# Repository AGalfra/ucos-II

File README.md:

# ucos-II

## Sensor de Temperatura ST-1820

Introducción

Este dispositivo desarrollado en el presente informe es un medidor de temperaturas basado en sensores 1-Wire del tipo  capaz de medir hasta 4 sensores simultáneamente (aunque esta limitación está dada solo por configuración del firmware para adaptarla a las opciones del menú).
Tiene además la posibilidad de modificar la escala de medición, es decir, en ºC y ºF.
También es configurable la frecuencia de adquisición de los sensores (3, 5 o 10 segundos).
Para la visualización de las temperaturas se pueden elegir entre 2 modos de operación que serán descritos más adelante.

Diseño del PCB en Kicad
Desarrollo del firmware en STM32CubeIDE con kernel U/COS-II
Descripción
 
Para este proyecto se utilizó la placa de desarrollo Blue Pill que cuenta con un microprocesador ARM Cortex-M3 STM32F103C8T6 de ST Microelectronics en el cual se ha embebido el Kernel v2.9216. 

Además de la placa de desarrollo se han utilizado los siguientes elementos:

-Pantalla OLED SSD1306 128x64 pixeles de 0.96” con comunicación I2C.

-Encoder rotativo, que es utilizado para controlar el dispositivo.

-Sensores de temperatura del tipo 1-Wire como por ej. los DS18B20, DS1820 o DS18S20.

-UART para poder realizar una conexión con la PC (para un menú de diagnóstico).

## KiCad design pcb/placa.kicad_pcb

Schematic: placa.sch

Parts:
J1, J2, J3, J4: Conn_01x03; PinHeader_1x03_P2.54mm_Horizontal
J5: UART; PinHeader_1x04_P2.54mm_Vertical
J6: Encoder; Encoder_Rotativo
R1: 4K7; R_Axial_DIN0204_L3.6mm_D1.6mm_P7.62mm_Horizontal
U1: Blue_Pill
U2: SSD1306

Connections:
+3V3: J1.3, J2.3, J3.3, J4.3, J5.1, J6.2, R1.1, U1.18, U1.40, U2.2
/DQ: J1.2, J2.2, J3.2, J4.2, R1.2, U1.30
/EBUT: J6.3, U1.31
/ENCA: J6.4, U1.13
/ENCB: J6.5, U1.14
/RX: J5.2, U1.27
/SCL: U1.34, U2.3
/SDA: U1.35, U2.4
/TX: J5.3, U1.26
GND: J1.1, J2.1, J3.1, J4.1, J5.4, J6.1, U1.19, U1.20, U1.39, U2.1

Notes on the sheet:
BUS ONEWIRE

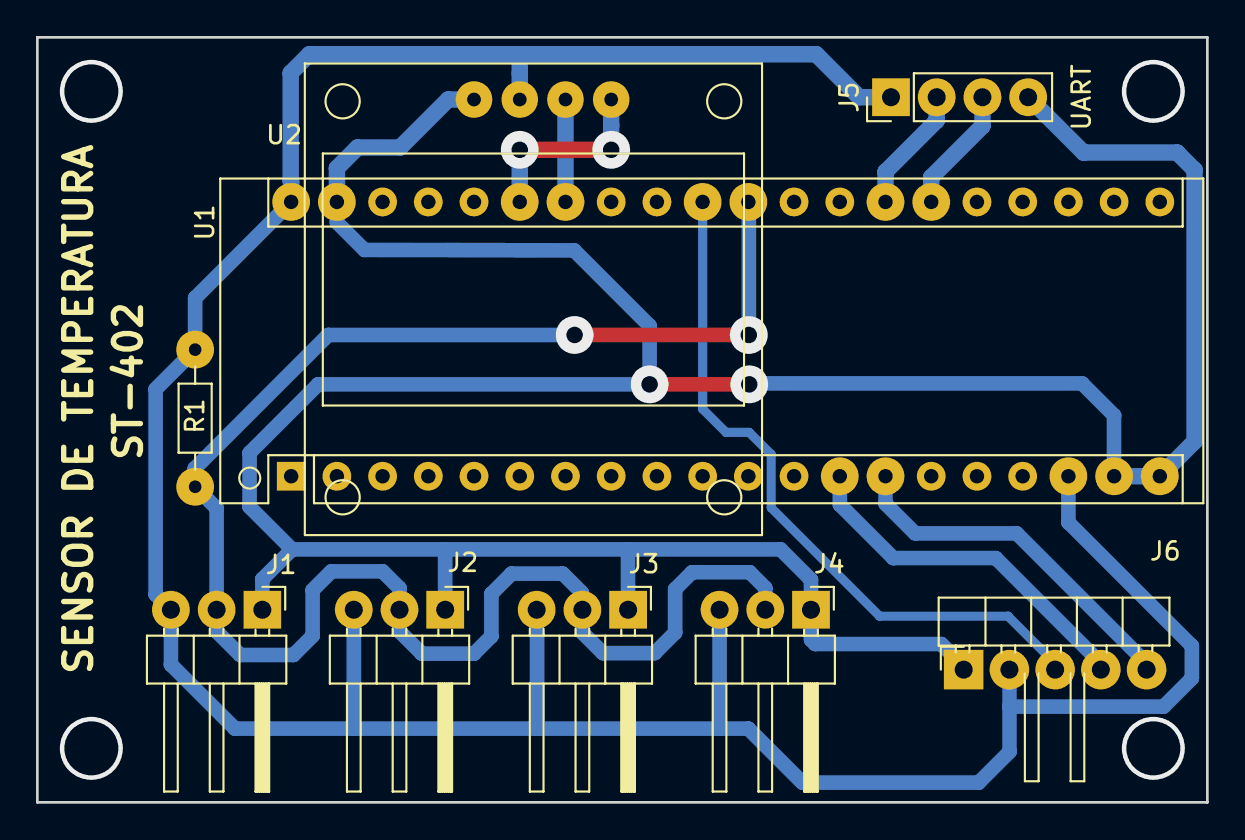
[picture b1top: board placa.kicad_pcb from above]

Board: 2 copper layers, 65.0 x 42.5 mm, 9 parts (0 on the bottom side), 10 nets.

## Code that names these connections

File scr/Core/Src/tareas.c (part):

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* Return(s)   : none.
* Caller(s)   : This is a task.
* Note(s)     : Esta tarea se ejecuta cada vez que se activan cualquiera de los sig. flags:
* 				ENCA: deteccion de flanco descendente en pin Encoder A.
* 				EBUT: deteccion de flanco descendente en pin Button.
*
* 				Los flags ENCA y EBUT son seteados en EdgeAFnct() y EdgeButFnct() que son las funciones
* 				callback de deteccion de flancos del modulo DIO
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 DICfgMode(0, DI_MODE_EDGE_LOW_GOING);					// deteccion de flancos descendentes en EncA
 DICfgEdgeDetectFnct(0, EdgeAFnct, (void *)flag_grp);	// EdgeAFnct: callback para señalizar los flag

 DICfgMode(1, DI_MODE_DIRECT);							// pin de EncB

 DICfgMode(3, DI_MODE_EDGE_LOW_GOING);					// pin de Button
 DICfgEdgeDetectFnct(3, EdgeButFnct, (void *)flag_grp);	// EdgeButFnct: callback para señalizar los flag
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
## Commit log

2023-05-04 Update README.md
    commit inicial
2023-05-04 source code
2023-05-04 Update README.md
    modificacion
2023-05-04 mover fotos
